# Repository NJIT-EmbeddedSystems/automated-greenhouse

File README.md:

# NJIT IEEE Embedded Systems
## Automated Greenhouse

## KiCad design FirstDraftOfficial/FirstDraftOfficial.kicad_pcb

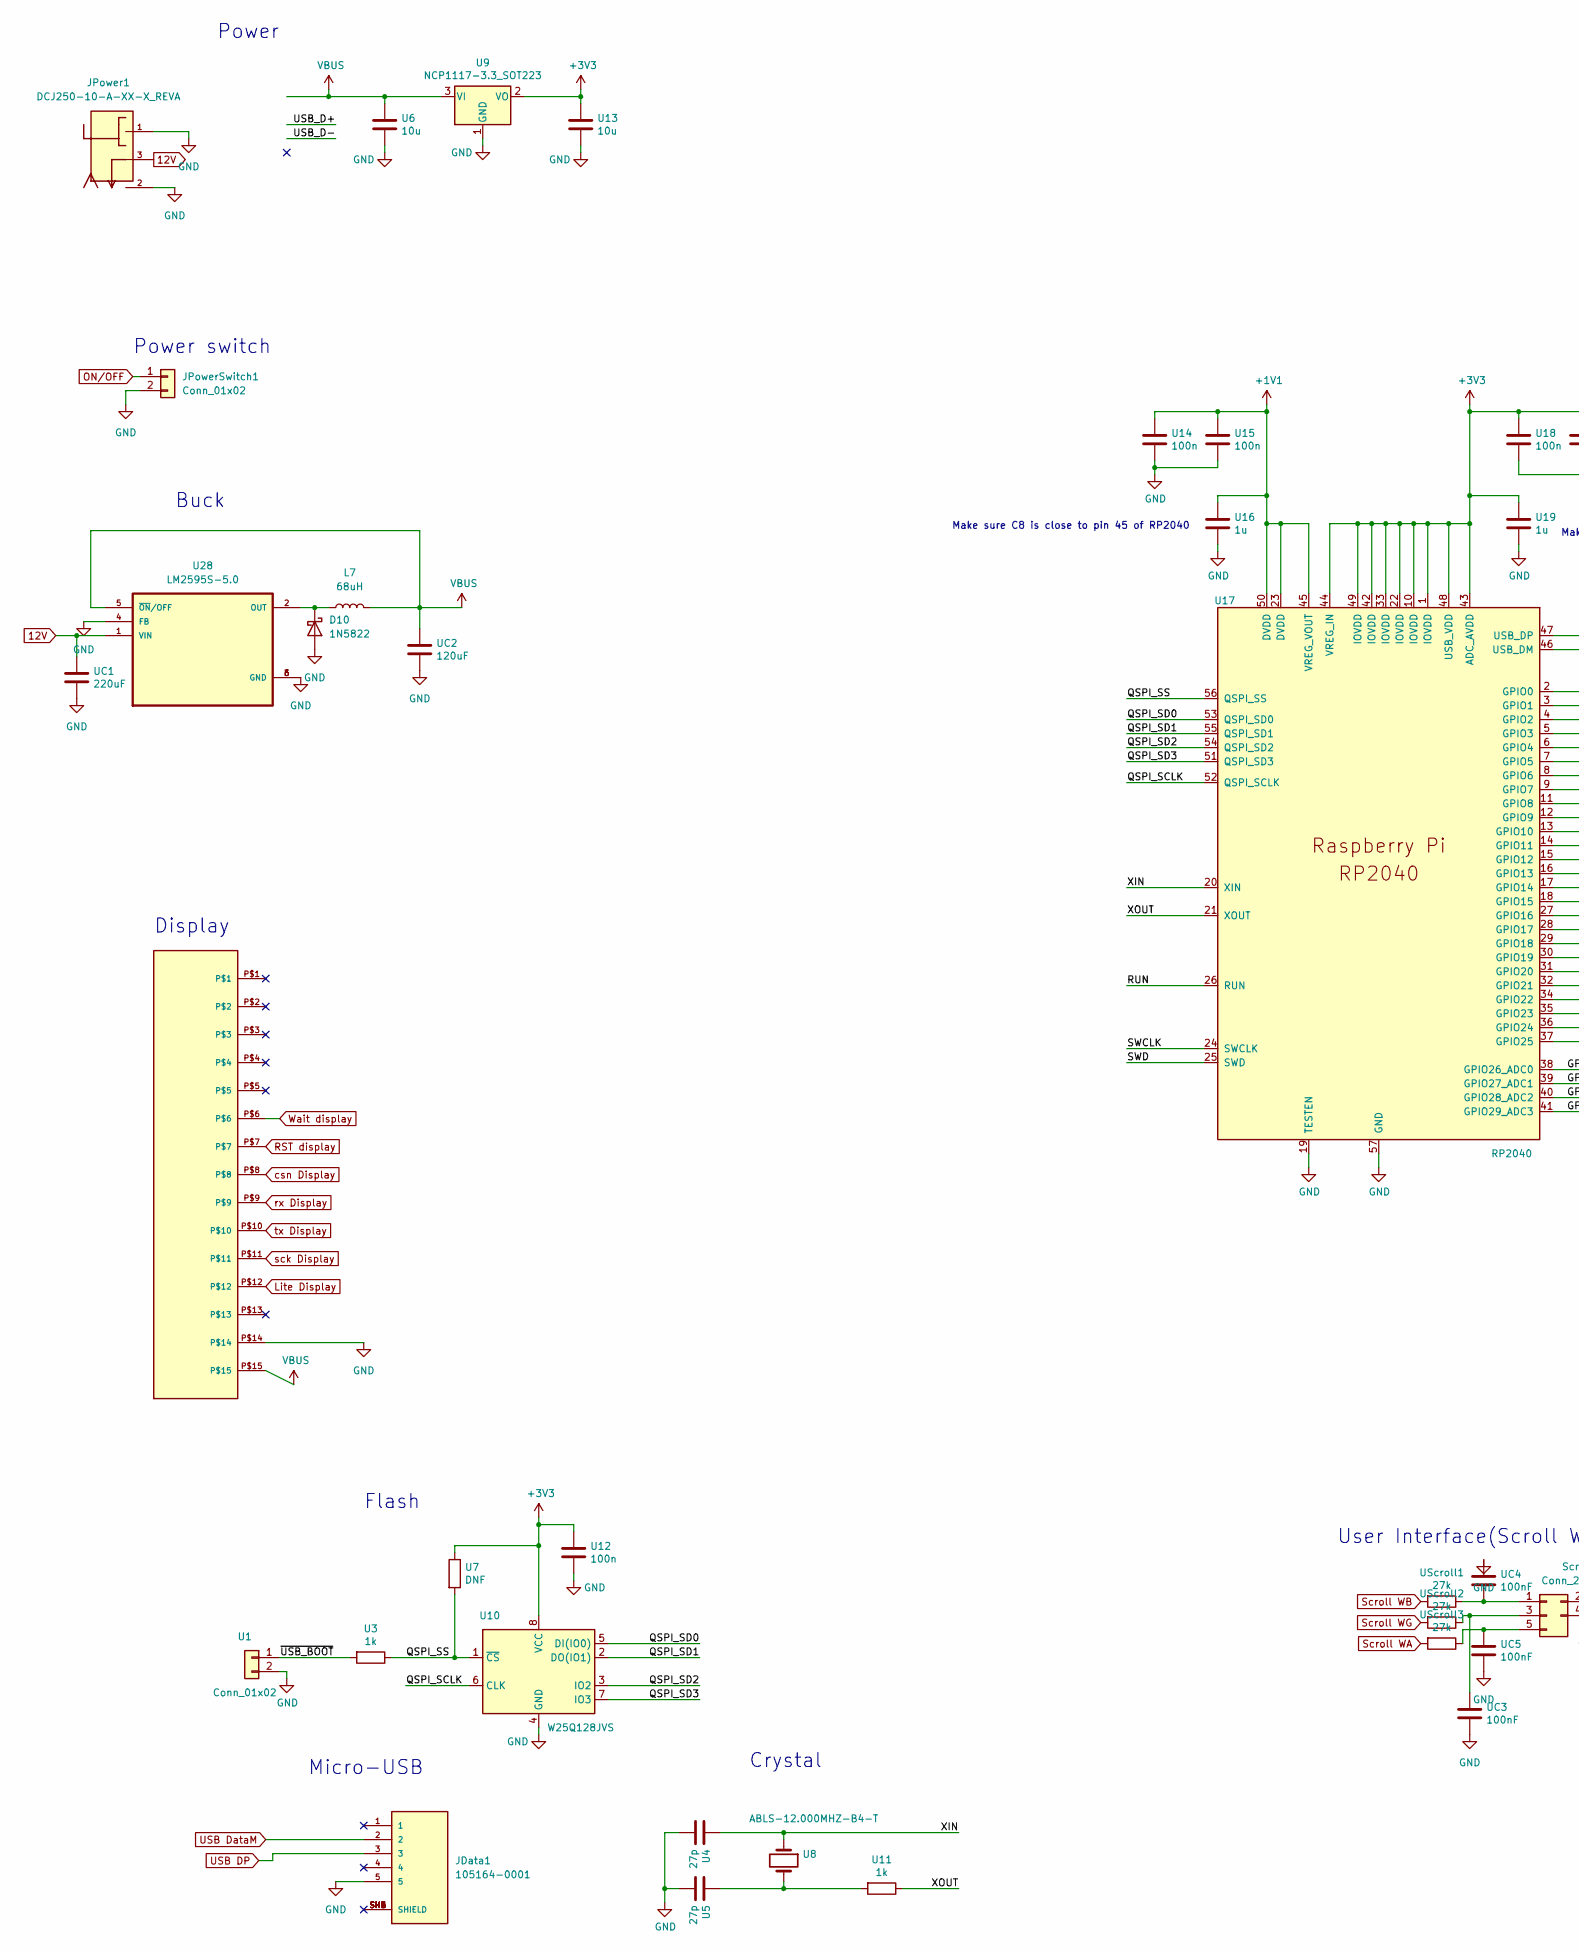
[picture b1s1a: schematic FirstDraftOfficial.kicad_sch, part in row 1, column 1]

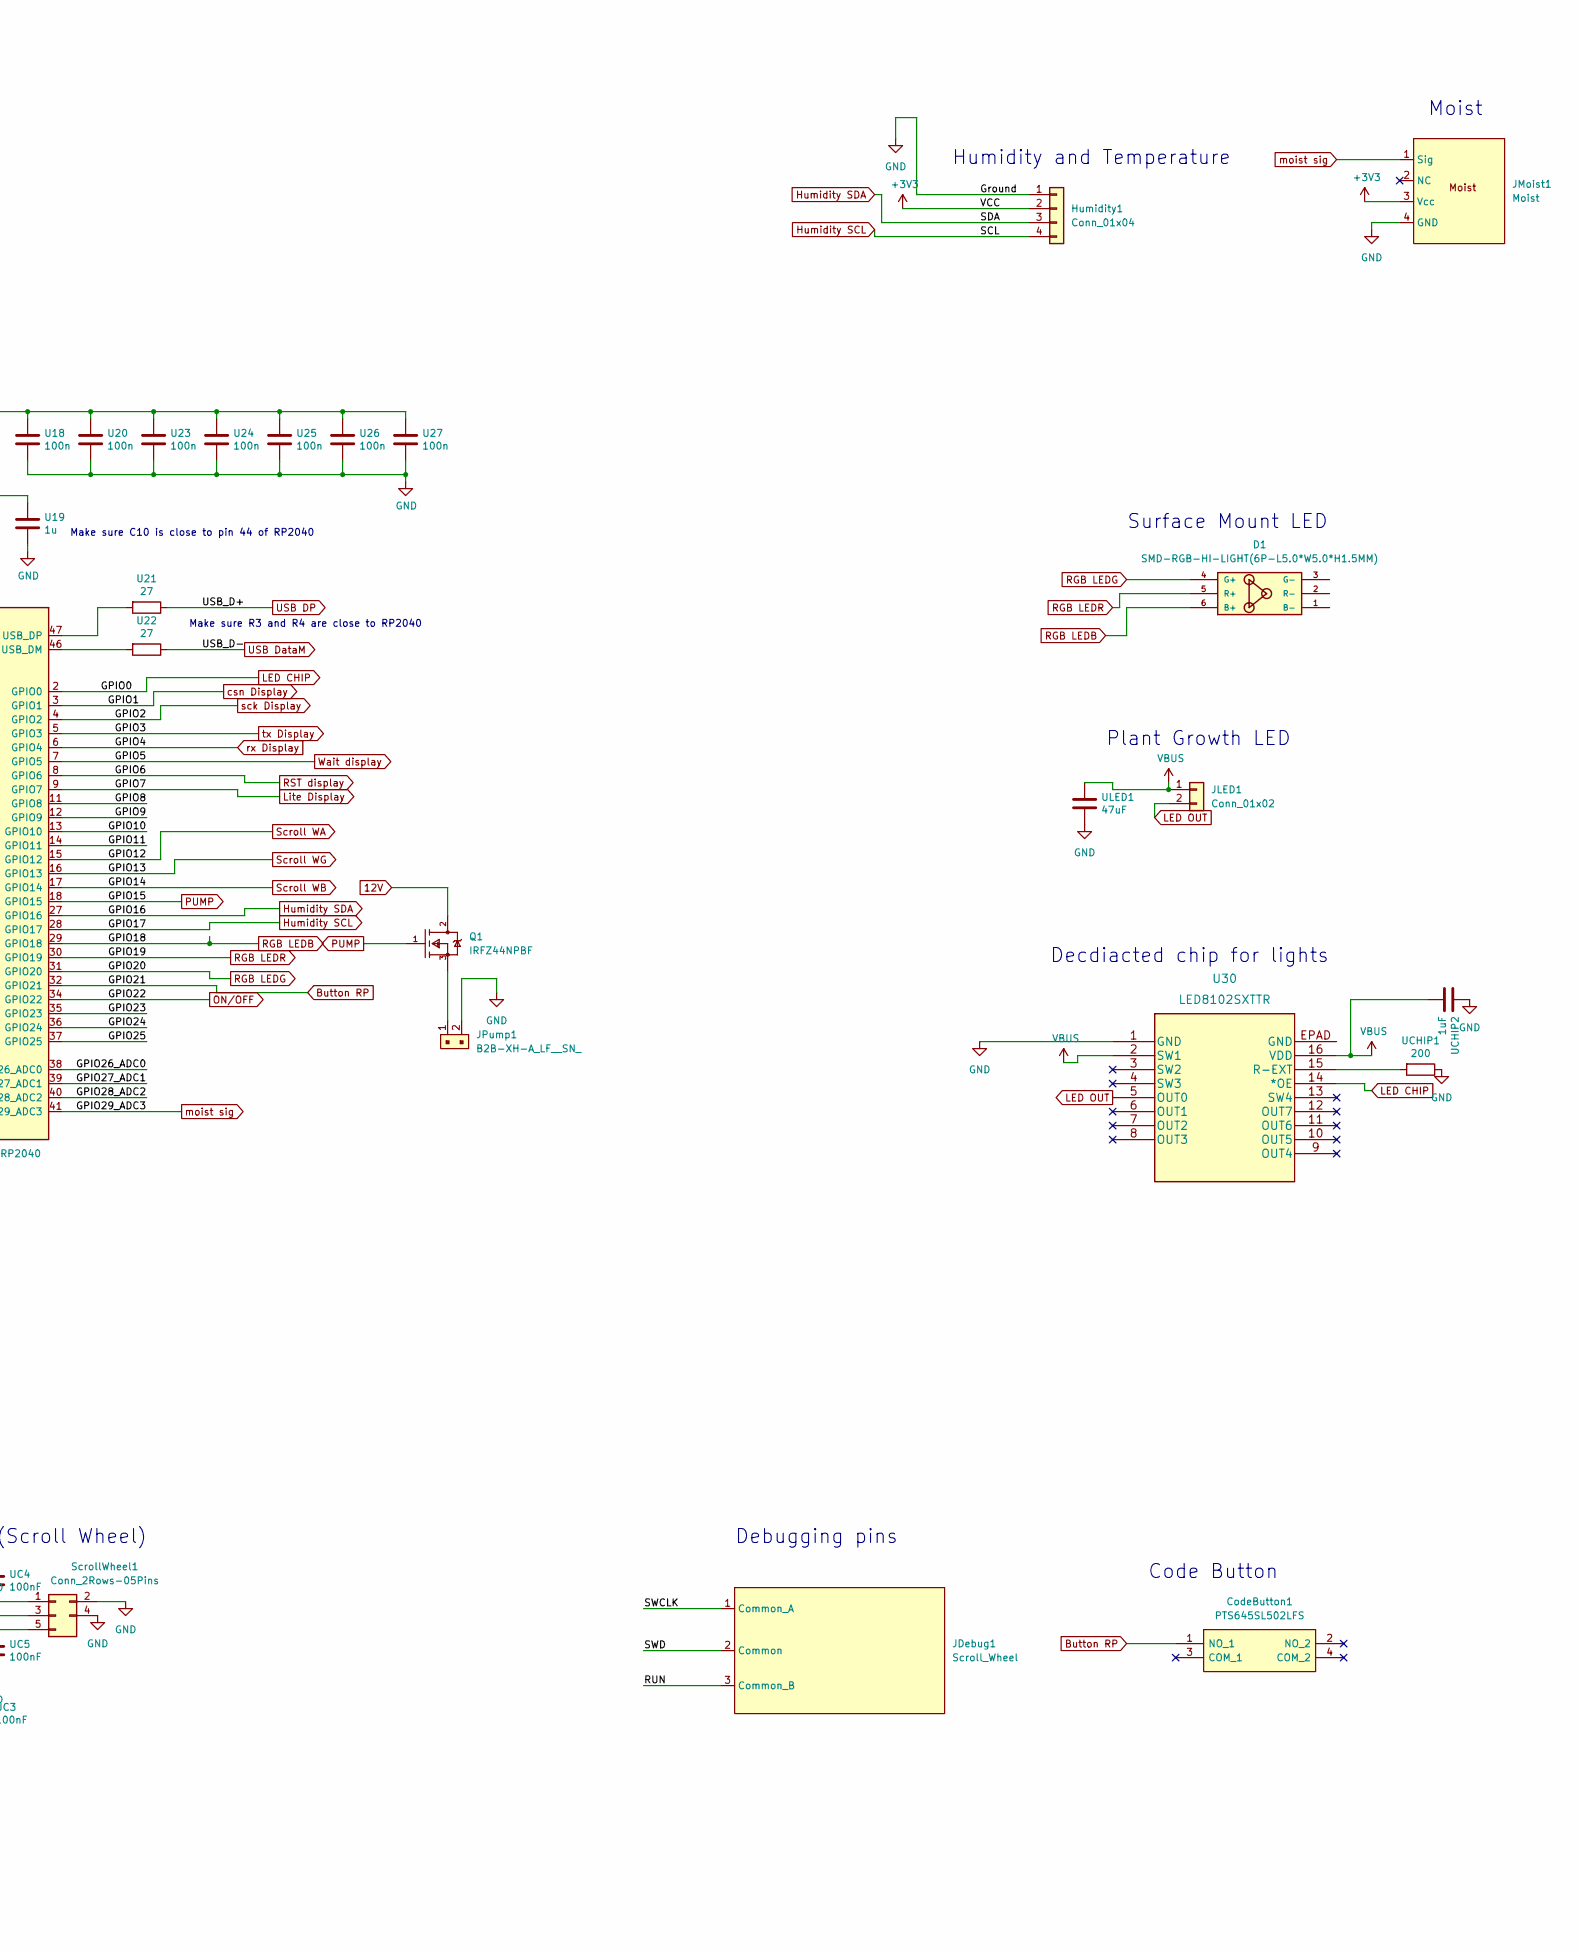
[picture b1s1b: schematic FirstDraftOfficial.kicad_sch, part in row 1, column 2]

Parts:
CodeButton1: PTS645SL502LFS; Manufacturer_Part_Number PTS645SL502LFS; Mouser Part Number 611-PTS645SL502
D1: SMD-RGB-HI-LIGHT(6P-L5.0*W5.0*H1.5MM); LED_RGB_5050-6; MPN 5050RGB
D10: 1N5822; D_DO-201AD_P15.24mm_Horizontal
Humidity1: Conn_01x04; 5112504020001
JData1: 105164-0001; MOLEX_105164-0001; PARTREV B
JDebug1: Scroll_Wheel; TE_1318123-1
JDisplay2: PPTC151LFBN-RC
JLED1: Conn_01x02; TE_1318123-1
JMoist1: Moist; 5112504020001
JPower1: DCJ250-10-A-XX-X_REVA; GCT_DCJ250-10-A-XX-X_REVA; PARTREV A
JPowerSwitch1: Conn_01x02; TE_1318123-1
JPump1: B2B-XH-A_LF__SN_; TE_1318123-1; MPN B2B-XH-A(LF)(SN); Digi-Key_PN 455-2247-ND
L7: 68uH; L_6.3x6.3_H3
Q1: IRFZ44NPBF; TO254P1016X419X2286-3; mouser part number 942-IRFZ44NPBF; digikey description N-Channel 55V 49A (Tc) 94W (Tc) Through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
ScrollWheel1: Conn_2Rows-05Pins; PPTC051LFBN-RC
U1: Conn_01x02; PinHeader_1x02_P2.54mm_Vertical
U3: 1k; C_0402_1005Metric
U4, U5: 27p; C_0402_1005Metric
U6, U13: 10u; C_0805_2012Metric
U7: DNF; C_0402_1005Metric
U8: ABLS-12.000MHZ-B4-T; XTAL_ABLS-12.000MHZ-B4-T
U9: NCP1117-3.3_SOT223; SOT-223-3_TabPin2
U10: W25Q128JVS; SOIC-8_5.23x5.23mm_P1.27mm
U11: 1k; R_0603_1608Metric
U12, U14, U15, U18, U20, U23, U24, U25, U26, U27: 100n; C_0402_1005Metric
U16, U19: 1u; C_0402_1005Metric
U17: RP2040; QFN40P700X700X90-57N
U21, U22: 27; R_0603_1608Metric_Pad0.98x0.95mm_HandSolder
U28: LM2595S-5.0; VREG_TPS79625KTTR
U30: LED8102SXTTR
UC1: 220uF; C_0402_1005Metric
UC2: 120uF; C_0402_1005Metric
UC3, UC4, UC5: 100nF; C_0402_1005Metric
UCHIP1: 200; C_0402_1005Metric
UCHIP2: 1uF; C_0402_1005Metric
ULED1: 47uF; C_0402_1005Metric
UScroll1, UScroll2, UScroll3: 27k; R_0603_1608Metric

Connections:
12V: JPower1.3, Q1.2 (DRAIN), U28.1 (VIN), UC1.1
+1V1: U14.1, U15.1, U16.1, U17.23 (DVDD), U17.45 (VREG_VOUT), U17.50 (DVDD)
+3V3: Humidity1.2, JMoist1.3 (Vcc), U7.1, U9.2 (VO), U10.8 (VCC), U12.1, U13.1, U17.1 (IOVDD), U17.10 (IOVDD), U17.22 (IOVDD), U17.33 (IOVDD), U17.42 (IOVDD), U17.43 (ADC_AVDD), U17.44 (VREG_IN), U17.48 (USB_VDD), U17.49 (IOVDD), U18.1, U19.1, U20.1, U23.1, U24.1, U25.1, U26.1, U27.1
/GPIO8: U17.11 (GPIO8)
/GPIO9: U17.12 (GPIO9)
/GPIO10: U17.13 (GPIO10)
/GPIO11: U17.14 (GPIO11)
/GPIO23: U17.35 (GPIO23)
/GPIO24: U17.36 (GPIO24)
/GPIO25: U17.37 (GPIO25)
/GPIO26_ADC0: U17.38 (GPIO26_ADC0)
/GPIO27_ADC1: U17.39 (GPIO27_ADC1)
/GPIO28_ADC2: U17.40 (GPIO28_ADC2)
/QSPI_SCLK: U10.6 (CLK), U17.52 (QSPI_SCLK)
/QSPI_SD0: U10.5 (DI(IO0)), U17.53 (QSPI_SD0)
/QSPI_SD1: U10.2 (DO(IO1)), U17.55 (QSPI_SD1)
/QSPI_SD2: U10.3 (IO2), U17.54 (QSPI_SD2)
/QSPI_SD3: U10.7 (IO3), U17.51 (QSPI_SD3)
/QSPI_SS: U3.1, U7.2, U10.1 (~CS), U17.56 (QSPI_SS)
/RUN: JDebug1.3 (Common_B), U17.26 (RUN)
/SWCLK: JDebug1.1 (Common_A), U17.24 (SWCLK)
/SWD: JDebug1.2 (Common), U17.25 (SWD)
/XIN: U4.1, U8.1, U17.20 (XIN)
/XOUT: U11.1, U17.21 (XOUT)
/~USB_BOOT: U1.1, U3.2
Button RP: CodeButton1.1 (NO_1), U17.32 (GPIO21)
GND: D10.2 (A), Humidity1.1, JData1.5, JDisplay2.P$14, JMoist1.4 (GND), JPower1.1, JPower1.2, JPowerSwitch1.2, JPump1.2, ScrollWheel1.2, ScrollWheel1.4, U1.2, U4.2, U5.2, U6.2, U9.1 (GND), U10.4 (GND), U12.2, U13.2, U14.2, U15.2, U16.2, U17.19 (TESTEN), U17.57 (GND), U18.2, U19.2, U20.2, U23.2, U24.2, U25.2, U26.2, U27.2, U28.3 (GND), U28.4 (FB), U28.6 (GND), U30.1 (GND), UC1.2, UC2.2, UC3.2, UC4.1, UC5.2, UCHIP1.1, UCHIP2.1, ULED1.2
Humidity SCL: Humidity1.4, U17.28 (GPIO17)
Humidity SDA: Humidity1.3, U17.27 (GPIO16)
LED CHIP: U17.2 (GPIO0), U30.14 (*OE)
LED OUT: JLED1.2, U30.5 (OUT0)
Lite Display: JDisplay2.P$12, U17.9 (GPIO7)
unnamed: D10.1 (K), L7.1, U28.2 (OUT)
unnamed: JPump1.1, Q1.3 (SOURCE)
unnamed: ScrollWheel1.1, UC4.2, UScroll1.1
unnamed: ScrollWheel1.3, UC3.1, UScroll2.1
unnamed: ScrollWheel1.5, UC5.1, UScroll3.1
unnamed: U5.1, U8.2, U11.2
unnamed: U17.46 (USB_DM), U22.2
unnamed: U17.47 (USB_DP), U21.2
unnamed: U30.15 (R-EXT), UCHIP1.2
ON/OFF: JPowerSwitch1.1, U17.34 (GPIO22)
PUMP: Q1.1 (GATE), U17.18 (GPIO15)
RGB LEDB: D1.6 (B+), U17.29 (GPIO18)
RGB LEDG: D1.4 (G+), U17.31 (GPIO20)
RGB LEDR: D1.5 (R+), U17.30 (GPIO19)
RST display: JDisplay2.P$7, U17.8 (GPIO6)
Scroll WA: U17.15 (GPIO12), UScroll3.2
Scroll WB: U17.17 (GPIO14), UScroll1.2
Scroll WG: U17.16 (GPIO13), UScroll2.2
USB DP: JData1.3, U21.1
USB DataM: JData1.2, U22.1
VBUS: JDisplay2.P$15, JLED1.1, L7.2, U6.1, U9.3 (VI), U28.5 (~ON/OFF), U30.2 (SW1), U30.16 (VDD), UC2.1, UCHIP2.2, ULED1.1
Wait display: JDisplay2.P$6, U17.7 (GPIO5)
csn Display: JDisplay2.P$8, U17.3 (GPIO1)
moist sig: JMoist1.1 (Sig), U17.41 (GPIO29_ADC3)
rx Display: JDisplay2.P$9, U17.6 (GPIO4)
sck Display: JDisplay2.P$11, U17.4 (GPIO2)
tx Display: JDisplay2.P$10, U17.5 (GPIO3)

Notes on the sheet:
Plant Growth LED
User Interface(Scroll Wheel)
Decdiacted chip for lights
Micro-USB
Make sure R3 and R4 are close to RP2040
Flash
Display
Humidity and Temperature
Make sure C10 is close to pin 44 of RP2040
Moist
Power
Surface Mount LED
Make sure C8 is close to pin 45 of RP2040
Buck
Debugging pins
Crystal
Code Button
Power switch

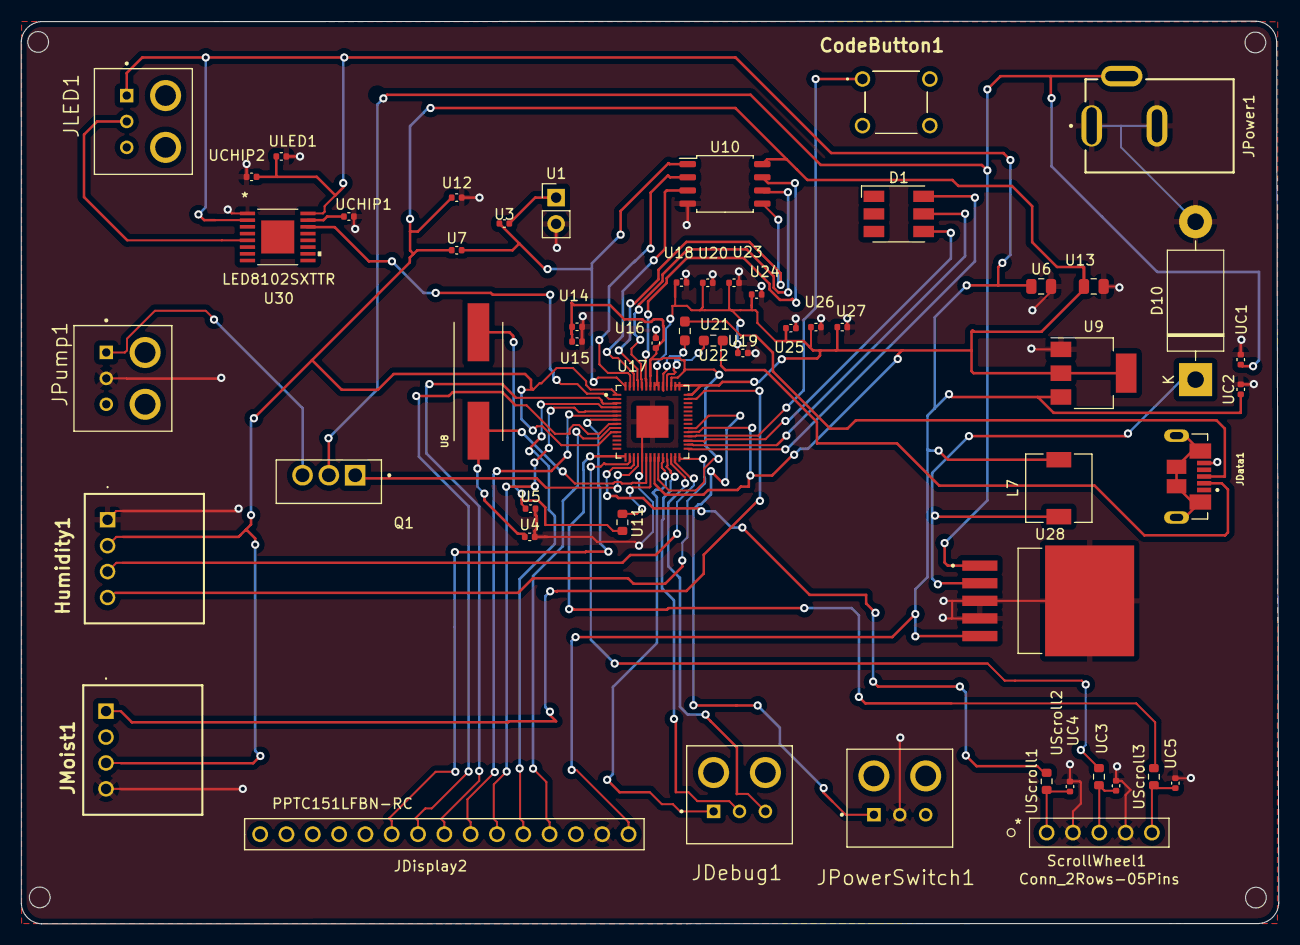
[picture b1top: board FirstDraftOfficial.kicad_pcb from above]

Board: 2 copper layers, 121.4 x 87.1 mm, 54 parts (0 on the bottom side), 49 nets.

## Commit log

2022-10-07 first pcb draft
2023-01-27 added Coding Group's file
2023-01-27 GUIslice port

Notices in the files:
parts and their libraries:
Copyright 2021 Accelerated Designs. All rights reserved.
